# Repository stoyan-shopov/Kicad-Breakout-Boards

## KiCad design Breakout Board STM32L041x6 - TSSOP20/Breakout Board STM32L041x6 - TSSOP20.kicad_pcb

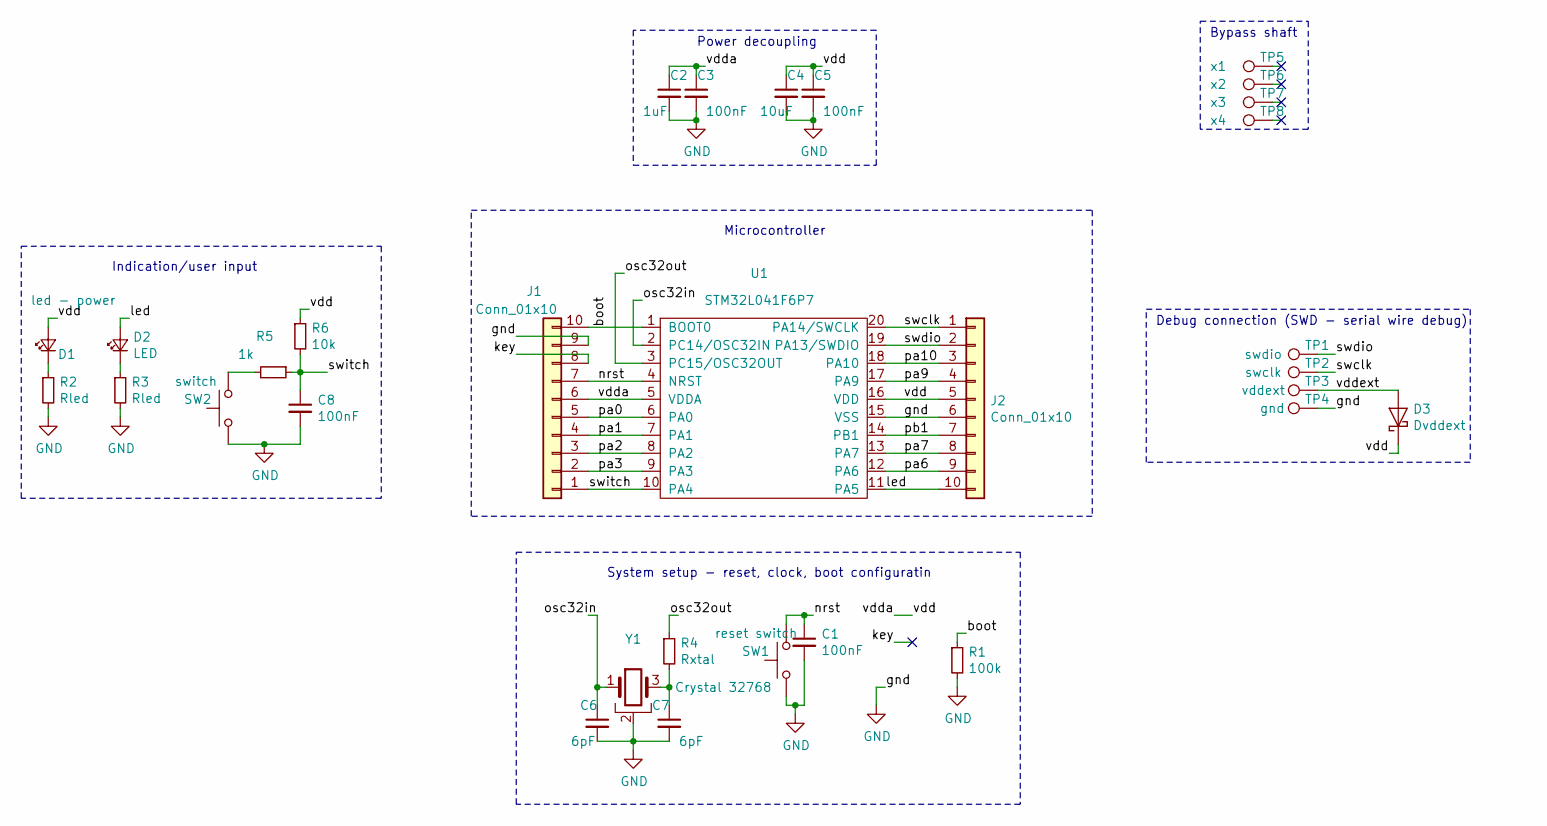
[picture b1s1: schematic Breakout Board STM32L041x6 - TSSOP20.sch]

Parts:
C1, C3, C5, C8: 100nF; D_0805_2012Metric_Pad1.15x1.40mm_HandSolder
C2: 1uF; D_0805_2012Metric_Pad1.15x1.40mm_HandSolder
C4: 10uF; D_0805_2012Metric_Pad1.15x1.40mm_HandSolder
C6, C7: 6pF; D_0805_2012Metric_Pad1.15x1.40mm_HandSolder
D1: led - power; LED_1206_3216Metric_Pad1.42x1.75mm_HandSolder
D2: LED; LED_1206_3216Metric_Pad1.42x1.75mm_HandSolder
D3: Dvddext; D_SOD-123
J1, J2: Conn_01x10; PinHeader 1x10 P2.54mm Vertical
R1: 100k; R_0805_2012Metric_Pad1.15x1.40mm_HandSolder
R2, R3: Rled; R_0805_2012Metric_Pad1.15x1.40mm_HandSolder
R4: Rxtal; R_0805_2012Metric_Pad1.15x1.40mm_HandSolder
R5: 1k; R_0805_2012Metric_Pad1.15x1.40mm_HandSolder
R6: 10k; R_0805_2012Metric_Pad1.15x1.40mm_HandSolder
SW1: reset switch; Tactile Switch TS-064 - Comet
SW2: switch; Tactile Switch TS-064 - Comet
TP1: swdio; TestPoint 2.54mm round
TP2: swclk; TestPoint 2.54mm round
TP3: vddext; TestPoint 2.54mm round
TP4: gnd; TestPoint 2.54mm square
TP5: x1; TestPoint 2.54mm round
TP6: x2; TestPoint 2.54mm round
TP7: x3; TestPoint 2.54mm round
TP8: x4; TestPoint 2.54mm round
U1: STM32L041F6P7; STM32L041x6 - TSSOP20
Y1: Crystal 32768; Crystal 32768 Hz Citizen - CMR200T32.768KDZB-UT

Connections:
/boot: J1.10, R1.1, U1.1 (BOOT0)
/key: J1.8
/led: D2.2 (A), J2.10, U1.11 (PA5)
/nrst: C1.1, J1.7, SW1.2, U1.4 (NRST)
/osc32in: C6.1, U1.2 (PC14/OSC32IN), Y1.1
/osc32out: R4.1, U1.3 (PC15/OSC32OUT)
/pa0: J1.5, U1.6 (PA0)
/pa1: J1.4, U1.7 (PA1)
/pa2: J1.3, U1.8 (PA2)
/pa3: J1.2, U1.9 (PA3)
/pa6: J2.9, U1.12 (PA6)
/pa7: J2.8, U1.13 (PA7)
/pa9: J2.4, U1.17 (PA9)
/pa10: J2.3, U1.18 (PA10)
/pb1: J2.7, U1.14 (PB1)
/swclk: J2.1, TP2.1, U1.20 (PA14/SWCLK)
/swdio: J2.2, TP1.1, U1.19 (PA13/SWDIO)
/switch: C8.1, J1.1, R5.1, R6.2, U1.10 (PA4)
/vdd: C2.1, C3.1, C4.1, C5.1, D1.2 (A), D3.1 (K), J1.6, J2.5, R6.1, U1.5 (VDDA), U1.16 (VDD)
/vddext: D3.2 (A), TP3.1
GND: C1.2, C2.2, C3.2, C4.2, C5.2, C6.2, C7.2, C8.2, J1.9, J2.6, R1.2, R2.2, R3.2, SW1.1, SW2.1, TP4.1, U1.15 (VSS), Y1.2
unnamed: C7.1, R4.2, Y1.3
unnamed: D1.1 (K), R2.1
unnamed: D2.1 (K), R3.1
unnamed: R5.2, SW2.2

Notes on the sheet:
Power decoupling
Debug connection (SWD - serial wire debug)
Indication/user input
Microcontroller
System setup - reset, clock, boot configuratin
Bypass shaft

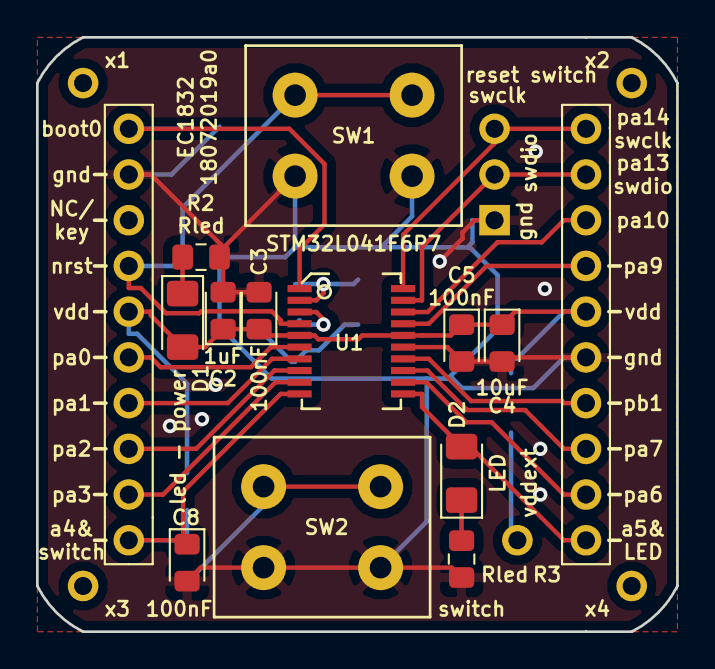
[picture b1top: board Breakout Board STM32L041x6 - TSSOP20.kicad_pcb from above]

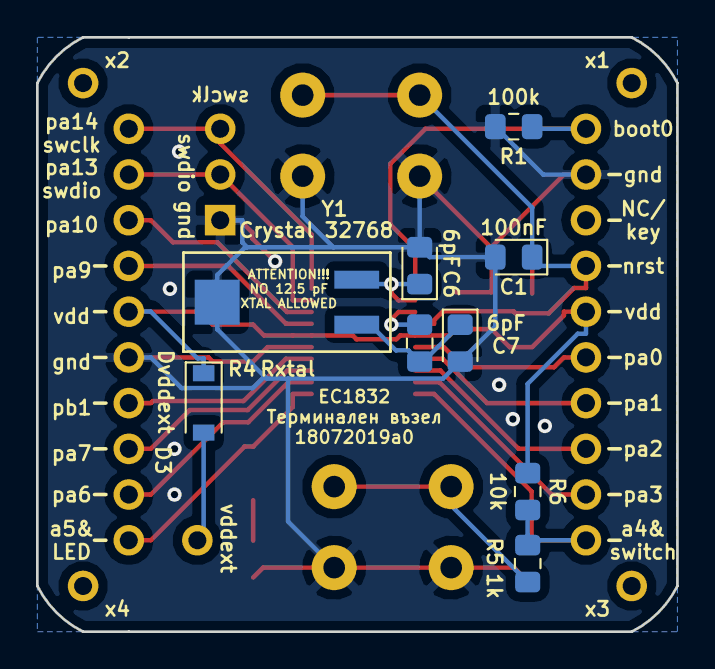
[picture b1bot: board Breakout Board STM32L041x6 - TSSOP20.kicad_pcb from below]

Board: 2 copper layers, 35.6 x 33.0 mm, 31 parts (9 on the bottom side), 24 nets.

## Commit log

2019-07-15 Create footprint library
2019-07-17 Add insignia
2019-07-17 Improve insignia
2019-07-17 Update - DRC check drill sizes - whatever, for this board
2019-07-18 Add ground vias and ground fill zones
2019-07-18 Generate fabrication files for first revision
